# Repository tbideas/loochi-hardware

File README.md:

Hardware source files for TBIdeas lamp
======================================

This github project contains the source file for the different revisions and prototypes of our smart lamp called Illumi and then Loochi.

## License

    Copyright 2012 - TBIdeas.com
    Distributed under the CC-BY-SA license.
    http://creativecommons.org/licenses/by-sa/3.0/

## Loochi v0.4

Third prototype.

This one is very similar to 0.3 but instead of a Bluegiga BLE112 module, we use an Aircable module with its generic firmware (so it does not need any programming). This module is not yet publicly available but will be very soon. Until then, you can contact us if you would like to get some.

In this design, we have also removed the npn/pnp transistors that were used to drive the mosfet. We wanted to compare the performance with and without them.

The communication protocol is labeled as I2C between the BLE module and the attiny but you can also do SPI. We have not really decided which one we will stick to.

### Known problems and limitations

This board was designed before we had time to assemble the 0.3 so the same problem applies on the LED pads, and connections.

## Loochi v0.3

Second complete prototype designed and built by us.

There is only one board with the LED soldered directly on the board. The PCB is intended to be an aluminium core PCB. For prototypes we have used traditional FR4 boards (from the awesome oshpark.com). In any case you absolutely need a pretty big heatsink on the other side of the board.

This board design is a major rework over the previous version. The main goal was to reduce manufacturing cost so that more people could enjoy Loochi. Another major design decision was to drop Wifi. We could write a lot about that but the biggest arguments were: (1) Wifi seriously increases the costs of the solution and (2) the efforts required by the user to set-up a Wifi lamp are important.

Main characteristics:
 * One ATTiny 861A is used to control the current going through the LED and adjust the brightness
 * One BLE112 module from Bluegiga is used for Bluetooth Low Energy communication with the app, it acts as an SPI Master to the Attiny
 * There is no more dedicated chip for the LED PWM (to reduce costs)
 * Ledengin 10W RGGB Led soldered directly on the PCB
 * Funny fact: the board radius is 3.1415925 cm

You will find more information on how this board works in the source code of the AVR. Several versions are provided (with graduating levels of complexity).

We also plan to do a video to explain how it works. If you are interested, let us know and it will probably be done quicker!

### Known problems on the board layout

There are a few known problems on this PCB:
 * The LED footprint is wrong: the first green LED is backwards (stupid mistake when linking pads and signals)
 * The schematic uses the RESET pin of the uController but we decided later on to change that, the mapping used in the software is BSENSE connected to PB5 and BPWM connected to PB4 (which means the Blue PWM output is inverted but allows us to keep the RESET pin free)
 * The BLE112 module is very sensitive to the quality of the power supply, add an RC filter on its VCC
 * Remove Q4 and short its source and drain (otherwise you will get a shortcut) - Warning: this removes the reverse voltage protection

If you want to make your own, we suggest that you fix those before getting the board manufactured or wait for a new design from us that would not have those problems. Another option is always to cut some traces and put some small wires. This is what we have done.

## Illumi v0.2

__Note: We used to call this version Illumi - dont be surprised in the documentation and source code__

This is the first complete prototype completely designed and built by us.

It is a dual-board design: a board with the micro-controller and the Wifi card, and another board with the LED drivers.

Features of the motherboard:

 * Arduino-Leonardo clone running at 8Mhz - Programmable via a ICSP connector or through the USB cable (once the bootloader has been burnt). You can use the Arduino IDE to program it.
 * Wifi module RN-171 from Roving Networks with a wire antenna
 * Bluetooth 4 Low Energy BLE112 module from Bluegiga
 * Only 75mm by 50mm
 * Switching 3.3 V power supply
 
Features of the LED driver

 * Input voltage from ~5V to 20V (depends on the type of LED you want to power) - Compatible with all sorts of high power LEDs
 * Three LT3518 swiching regulator for a 700mA constant current source to drive one RGB led
 * PWM inputs to control the brightness of each component: Red, Green, Blue
 * Shutdown pin to turn off the regulators and save power
 * Three temperature sensors to measure the board temperature

### Files

 * illumi-motherboard.sch: Eagle Schematic for the motherboard
 * illumi-motherboard.sch: Eagle Board for the motherboard
 * illumi-leddriver.sch: Eagle Schematic for the LED Driver
 * illumi-leddriver.sch: Eagle Board for the LED Driver
 * illumi-leddriver.asc: LTSpice simulation for one LT3518 channel 
 * illumi-v0.2-bom.csv: Bill of material - Detailed list of parts with Mouser reference number, price, etc

### Other resources

 * Source code for the motherboard is available in the Github project named "illumi"
 * Configuration files for the Arduino environment to program this board is in the project named "illumi-arduino"
 * Blog articles:
 ** [3D renderings][blog-board3d]
 ** [Pictures of the assembled board][blog-v0.2]

### Known problems and limitations

 * On the motherboard, you must not solder R16 and bridge the pads instead. The idea was to build a low-pass filter with R16 and C13 but the voltage drop on AVCC is too high and the chip is not programmable with R16 in place. Check out [this discussion on electronics stackexchange][stackexchange-avcc] for more info.
 * The LED driver includes a LM317 to provide 3.3V to the three LT3518. Although they dont use much current, bringing a 20V input to 3.3V incurs some serious heat dissipation on the LM317. It works so far but the next designs will use the motherboard voltage regulator for 3.3V

## Illumi v0.1

This is a very cheap to build linear current source for high power RGB LEDs. Find out more and read more on the [blog article][blog-v0.1]. 

## Illumi v0.0

This is the simplest way to drive an RGB light. Those files were produced to prepare a [blog post introducing development for Illumi][blog-v0.0].

## Let's stay in touch!

We hope you will find this information useful! We are open-sourcing all of this in the hope that it will be useful to someone else - if it is, or if you have any question, please contact us: contact THE_AROBASE tbideas.com.

[blog-v0.0]: http://www.tbideas.com/blog/illumi-101-iphone-controlled-rgb-light/
[blog-v0.1]: http://www.tbideas.com/blog/build-an-arduino-shield-to-drive-high-power-rgb-led/
[stackexchange-avcc]: http://electronics.stackexchange.com/questions/36167/understanding-the-avcc-pin-wiring-on-arduinoleonardo-low-pass-filter
[blog-v0.2]: http://www.tbideas.com/blog/some-pictures-of-our-latest-prototype/
[blog-board3d]: http://www.tbideas.com/blog/design-of-the-led-driver/
[contact]: contact@tbideas.com

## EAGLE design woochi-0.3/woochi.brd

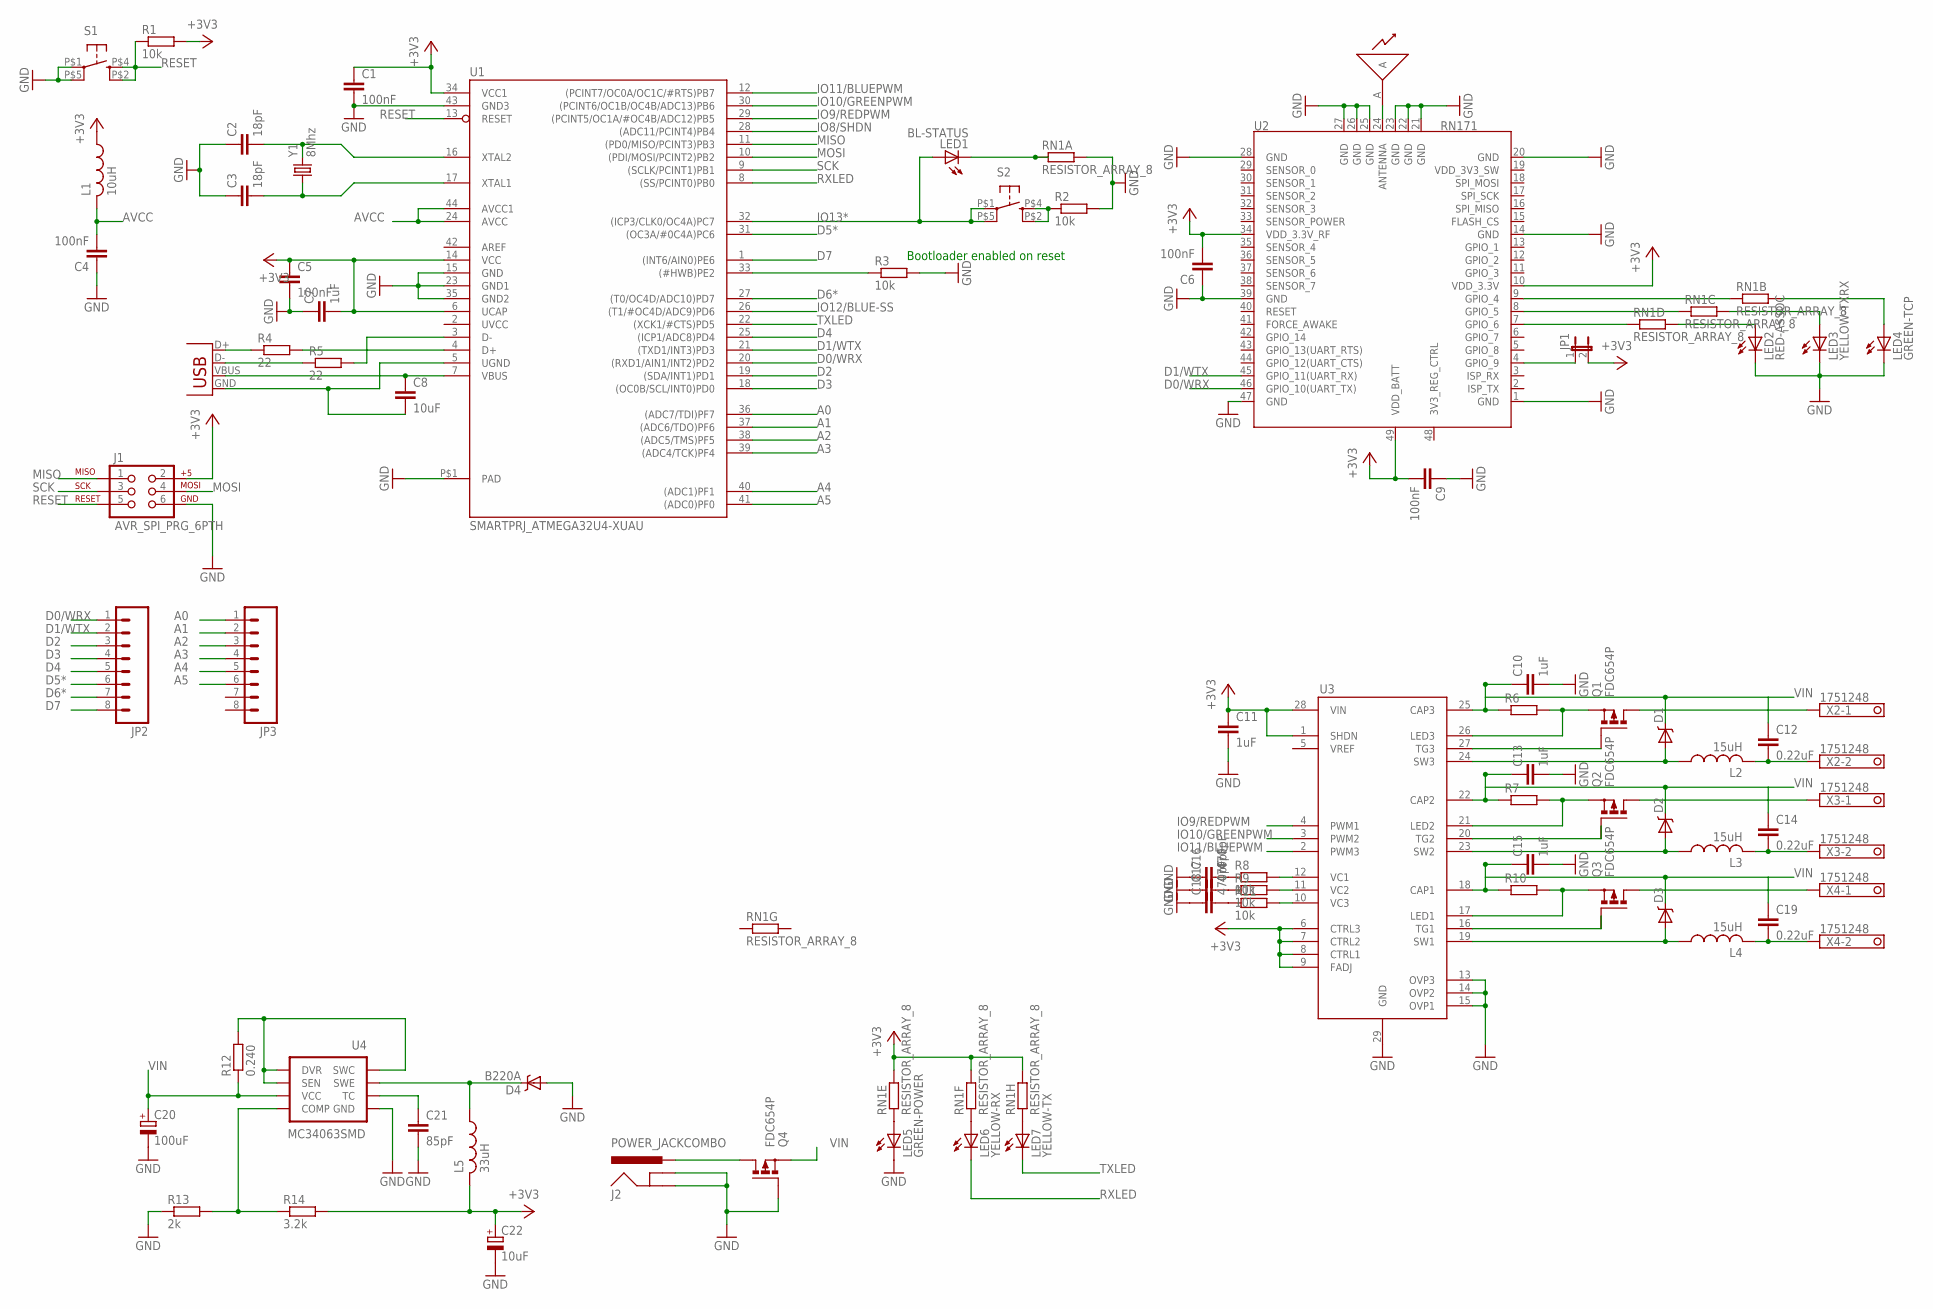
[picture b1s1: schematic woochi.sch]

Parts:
A1: ANTENNAWIRE; ANTENNA-WIRE
C1, C4, C5, C6, C9: 100nF; C0603
C2, C3: 18pF; C0603
C7, C10, C11, C13, C15: 1uF; C0603
C8: 10uF; C0603
C12, C14, C19: 0.22uF; C0603
C16, C17, C18: 470pF; C0603
C20: 100uF; PANASONIC_D
C21: 85pF; C0603
C22: 10uF; PANASONIC_C
D1, D2, D3: DIODE-SCHOTTKYBIGPAD; SMA-DIODE-BIG
D4: B220A; SMA-DIODE-BIG
J1: AVR_SPI_PRG_6PTH; 2X3
J2: POWER_JACKCOMBO; POWER_JACK_COMBO
JP1: JUMPER-2PTH; 1X02
JP2, JP3: M081X08; 1X08
L1: 10uH; L0603
L2, L3, L4: 15uH; BOURNS-6045
L5: 33uH; BOURNS-6045
LED1: BL-STATUS; SML0603
LED2: RED-ASSOC; SML0603
LED3: YELLOW-TXRX; SML0603
LED4: GREEN-TCP; SML0603
LED5: GREEN-POWER; SML0603
LED6: YELLOW-RX; SML0603
LED7: YELLOW-TX; SML0603
Q1, Q2, Q3, Q4: FDC654P; SUPERSOT6
R1, R2, R3, R8, R9, R11: 10k; R0603
R4, R5: 22; R0603
R6, R7, R10: R-EU_R0603; R0603
R12: 0.240; R0603
R13: 2k; R0603
R14: 3.2k; R0603
RN1: RESISTOR_ARRAY_8; CAT16-F8/CAT16-J8
S1, S2: TAC_SWITCH; CK-KMS_PEGS
U1: SMARTPRJ_ATMEGA32U4-XUAU; SMARTPRJ_TQFP44-PAD
U2: RN171; MODULE_49P-1.27-26.67X17.78
U3: LT3496; SSOP28_THERMAL
U4: MC34063SMD; SO08
X1: USB-MICROB
X2, X3, X4: 1751248
Y1: 8Mhz; HC49UP

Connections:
+3V3: C1.1, C5.1, C6.2, C7.2, C9.2, C11.1, C22.+, J1.2, JP1.2, L1.1, L5.P$2 (2), R1.2, R14.2, RN1.9 (2), RN1.11 (2), RN1.12 (2), U1.6 (UCAP), U1.14 (VCC), U1.34 (VCC1), U2.10 (VDD_3.3V), U2.34 (VDD_3.3V_RF), U2.49 (VDD_BATT), U3.1 (SHDN), U3.6 (CTRL3), U3.7 (CTRL2), U3.8 (CTRL1), U3.9 (FADJ), U3.28 (VIN)
A0: JP3.1, U1.36 ((ADC7/TDI)PF7)
A1: JP3.2, U1.37 ((ADC6/TDO)PF6)
A2: JP3.3, U1.38 ((ADC5/TMS)PF5)
A3: JP3.4, U1.39 ((ADC4/TCK)PF4)
A4: JP3.5, U1.40 ((ADC1)PF1)
A5: JP3.6, U1.41 ((ADC0)PF0)
AREF: U1.42 (AREF)
AVCC: C4.2, L1.2, U1.24 (AVCC), U1.44 (AVCC1)
D0/WRX: JP2.1, U1.20 ((RXD1/AIN1/INT2)PD2), U2.46 (GPIO_10(UART_TX))
D1/WTX: JP2.2, U1.21 ((TXD1/INT3)PD3), U2.45 (GPIO_11(UART_RX))
D2: JP2.3, U1.19 ((SDA/INT1)PD1)
D3: JP2.4, U1.18 ((OC0B/SCL/INT0)PD0)
D4: JP2.5, U1.25 ((ICP1/ADC8)PD4)
D5*: JP2.6, U1.31 ((OC3A/#0C4A)PC6)
D6*: JP2.7, U1.27 ((T0/OC4D/ADC10)PD7)
D7: JP2.8, U1.1 ((INT6/AIN0)PE6)
GND: C1.2, C2.1, C3.1, C4.1, C5.2, C6.1, C7.1, C9.1, C10.2, C11.2, C13.2, C15.2, C16.1, C17.1, C18.1, C20.-, C21.2, C22.-, D4.A, J1.6, J2.GND (GNDBREAK), J2.GND@1 (GND), LED2.C, LED3.C, LED4.C, LED5.C, Q4.P$3 (G), R2.2, R3.2, R13.1, RN1.16 (2), S1.P$1 (1), S1.P$5 (2), U1.15 (GND), U1.23 (GND1), U1.35 (GND2), U1.43 (GND3), U1.P$1 (PAD), U2.1 (GND), U2.14 (GND), U2.20 (GND), U2.21 (GND), U2.22 (GND), U2.23 (GND), U2.25 (GND), U2.26 (GND), U2.27 (GND), U2.28 (GND), U2.39 (GND), U2.47 (GND), U3.13 (OVP3), U3.14 (OVP2), U3.15 (OVP1), U3.29 (GND), U4.4 (GND)
IO8/SHDN: U1.28 ((ADC11/PCINT4)PB4)
IO9/REDPWM: U1.29 ((PCINT5/OC1A/#OC4B/ADC12)PB5), U3.4 (PWM1)
IO10/GREENPWM: U1.30 ((PCINT6/OC1B/OC4B/ADC13)PB6), U3.3 (PWM2)
IO11/BLUEPWM: U1.12 ((PCINT7/OC0A/OC1C/#RTS)PB7), U3.2 (PWM3)
IO12/BLUE-SS: U1.26 ((T1/#OC4D/ADC9)PD6)
IO13*: LED1.A, S2.P$1 (1), S2.P$5 (2), U1.32 ((ICP3/CLK0/OC4A)PC7)
MISO: J1.1, U1.11 ((PD0/MISO/PCINT3)PB3)
MOSI: J1.4, U1.10 ((PDI/MOSI/PCINT2)PB2)
unnamed: LED5.A, RN1.5 (1)
unnamed: A1.A, U2.24 (ANTENNA)
unnamed: RN1.2 (1), U2.9 (GPIO_4)
unnamed: RN1.3 (1), U2.8 (GPIO_5)
unnamed: RN1.4 (1), U2.7 (GPIO_6)
unnamed: LED2.A, RN1.13 (2)
unnamed: LED3.A, RN1.14 (2)
unnamed: LED4.A, RN1.15 (2)
unnamed: C8.2, U1.5 (UGND), X1.GND
unnamed: R4.1, X1.D+
unnamed: JP1.1, U2.4 (GPIO_9)
unnamed: R5.1, X1.D-
unnamed: C8.1, U1.7 (VBUS), X1.VBUS
unnamed: R4.2, U1.4 (D+)
unnamed: R5.2, U1.3 (D-)
unnamed: LED1.C, RN1.1
unnamed: LED6.A, RN1.6 (1)
unnamed: LED7.A, RN1.8 (1)
unnamed: R3.1, U1.33 ((#HWB)PE2)
unnamed: R12.2, U4.1 (SWC), U4.7 (SEN), U4.8 (DVR)
unnamed: J2.POWER (PWR), Q4.P$1 (D), Q4.P$2 (D), Q4.P$5 (D), Q4.P$6 (D)
unnamed: D4.C, L5.P$1 (1), U4.2 (SWE)
unnamed: R2.1, S2.P$2 (4), S2.P$4 (3)
unnamed: C21.1, U4.3 (TC)
unnamed: R13.2, R14.1, U4.5 (COMP)
unnamed: C12.2, L2.P$2 (2), X2.2
unnamed: Q1.P$4 (S), R6.2, U3.26 (LED3)
unnamed: D1.A, L2.P$1 (1), U3.24 (SW3)
unnamed: Q2.P$4 (S), R7.2, U3.21 (LED2)
unnamed: Q1.P$1 (D), Q1.P$2 (D), Q1.P$5 (D), Q1.P$6 (D), X2.1
unnamed: Q1.P$3 (G), U3.27 (TG3)
unnamed: C14.2, L3.P$2 (2), X3.2
unnamed: R11.2, U3.10 (VC3)
unnamed: R9.2, U3.11 (VC2)
unnamed: R8.2, U3.12 (VC1)
unnamed: C16.2, R8.1
unnamed: C17.2, R9.1
unnamed: C18.2, R11.1
unnamed: D2.A, L3.P$1 (1), U3.23 (SW2)
unnamed: Q2.P$3 (G), U3.20 (TG2)
unnamed: Q2.P$1 (D), Q2.P$2 (D), Q2.P$5 (D), Q2.P$6 (D), X3.1
unnamed: Q3.P$4 (S), R10.2, U3.17 (LED1)
unnamed: C19.2, L4.P$2 (2), X4.2
unnamed: D3.A, L4.P$1 (1), U3.19 (SW1)
unnamed: Q3.P$3 (G), U3.16 (TG1)
unnamed: Q3.P$1 (D), Q3.P$2 (D), Q3.P$5 (D), Q3.P$6 (D), X4.1
RESET: R1.1, S1.P$2 (4), S1.P$4 (3), U1.13 (RESET)
RXLED: LED6.C, U1.8 ((SS/PCINT0)PB0)
SCK: J1.3, U1.9 ((SCLK/PCINT1)PB1)
TXLED: LED7.C, U1.22 ((XCK1/#CTS)PD5)
UVCC: U1.2 (UVCC)
VIN: C10.1, C12.1, C13.1, C14.1, C15.1, C19.1, C20.+, D1.C, D2.C, D3.C, Q4.P$4 (S), R6.1, R7.1, R10.1, R12.1, U3.18 (CAP1), U3.22 (CAP2), U3.25 (CAP3), U4.6 (VCC)
XTAL1: C3.2, U1.17 (XTAL1), Y1.1
XTAL2: C2.2, U1.16 (XTAL2), Y1.2

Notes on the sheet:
Bootloader enabled on reset

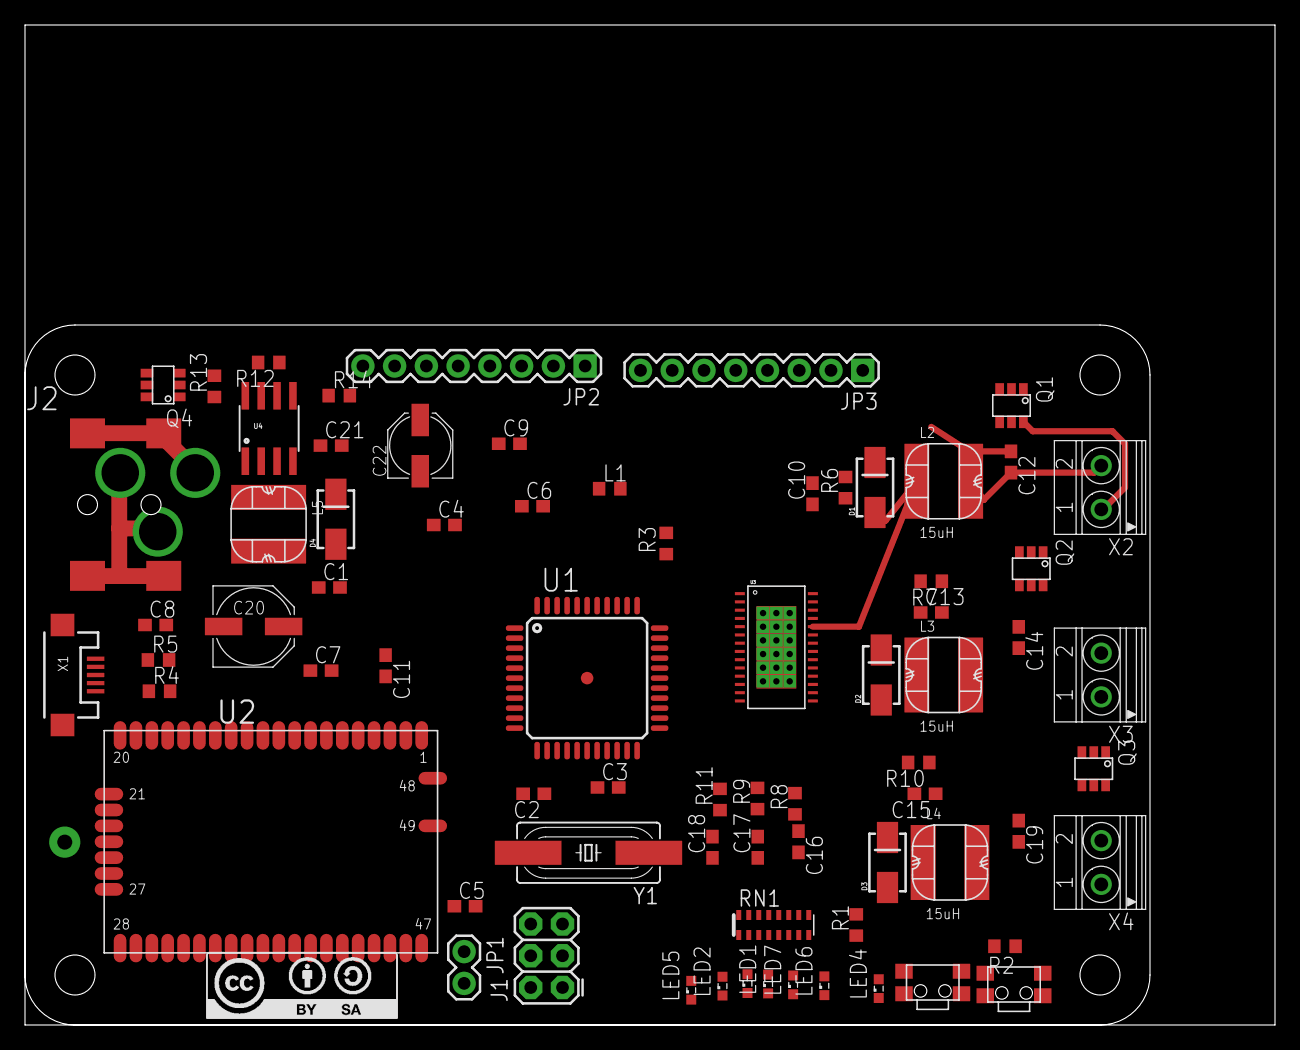
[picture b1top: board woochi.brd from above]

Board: 2 copper layers, 100.0 x 80.0 mm, 76 parts (0 on the bottom side), 76 nets.

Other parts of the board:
U$1: DP9056_V1
U$2: LOGO_CC-BY-SA

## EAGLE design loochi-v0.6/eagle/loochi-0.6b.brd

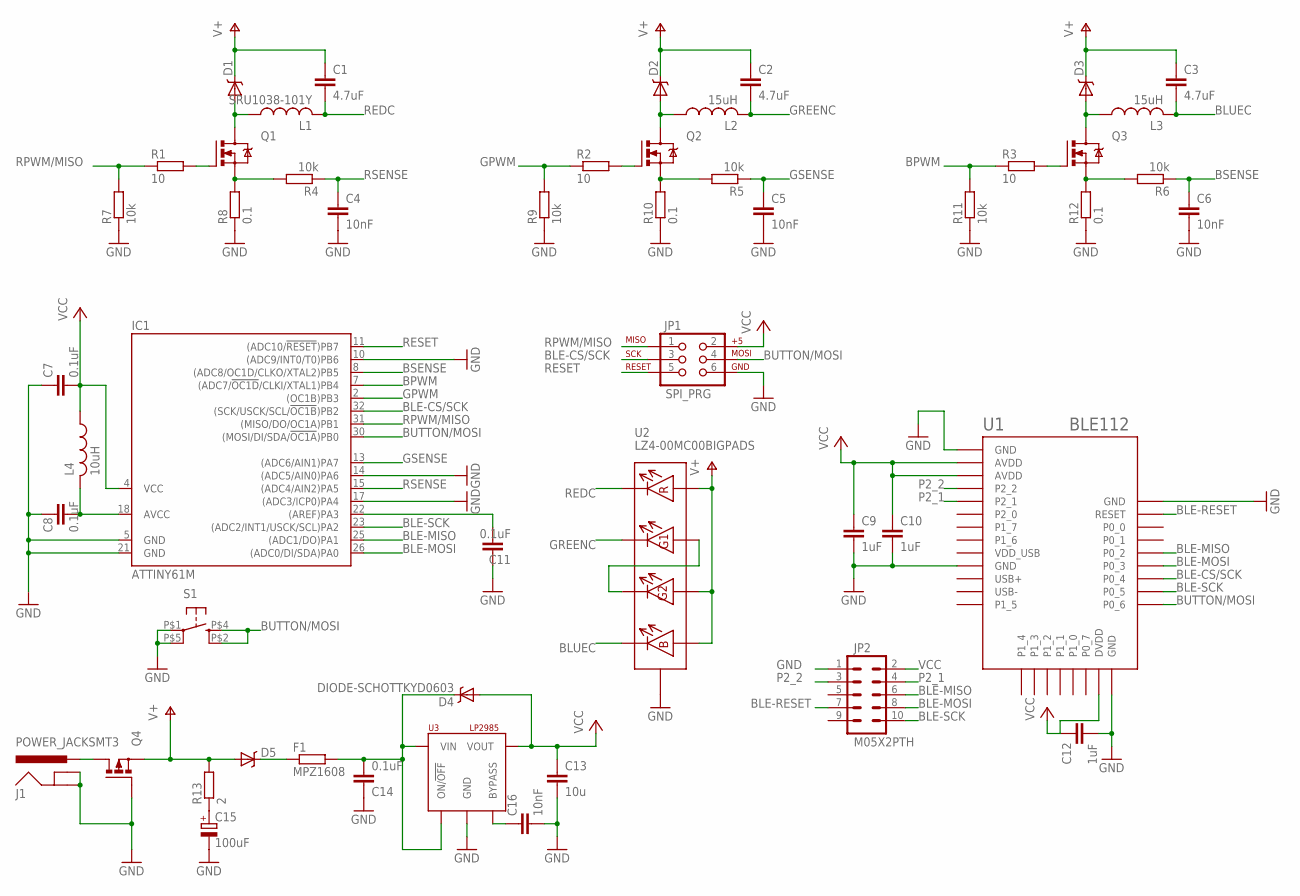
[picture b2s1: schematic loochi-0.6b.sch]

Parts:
C1, C2, C3: 4.7uF; C0603
C4, C5, C6, C16: 10nF; C0603
C7, C8, C11: 0.1uF; C0603
C9, C10, C12: 1uF; C0603
C13: 10u; C0603
C14: 0.1uF; C0603K
C15: 100uF; PANASONIC_D
D1, D2, D3, D5: PMEG4010CEH; SOD123F
D4: DIODE-SCHOTTKYD0603; D0603
F1: MPZ1608; R0603
IC1: ATTINY61M; MLF32
J1: POWER_JACKSMT3; POWER-KYCONSMT3
JP1: SPI_PRG; 2X3-NS
JP2: M05X2PTH; AVR_ICSP
L1: SRU1038-101Y; BOURNS-SRU1038
L2, L3: 15uH; BOURNS-SRU1038
L4: 10uH; L0603
Q1, Q2, Q3: PMN25ENSOT457; SOT457
Q4: FDC654P; SUPERSOT6
R1, R2, R3: 10; R0603
R4, R5, R6, R7, R9, R11: 10k; R0603
R8, R10, R12: 0.1; R0603
R13: 2; R0603
S1: TAC_SWITCH; CK-KMS_PEGS
U1: BLE112; SF-BLUEGIGA_BLE112-A
U2: LZ4-00MC00BIGPADS; LZ4-00MC00-BIGPADS
U3: LP2985; DBV

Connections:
BLE-CS/SCK: IC1.32 ((SCK/USCK/SCL/!OC1B!)PB2), JP1.3, U1.P0_4
BLE-MISO: IC1.25 ((ADC1/DO)PA1), JP2.6, U1.P0_2
BLE-MOSI: IC1.26 ((ADC0/DI/SDA)PA0), JP2.8, U1.P0_3
BLE-RESET: JP2.7, U1.RESET
BLE-SCK: IC1.23 ((ADC2/INT1/USCK/SCL)PA2), JP2.10, U1.P0_5
BLUEC: C3.2, L3.P$2 (2), U2.P$8
BPWM: IC1.7 ((ADC7/!OC1D!/CLKI/XTAL1)PB4), R3.1, R11.2
BSENSE: C6.1, IC1.8 ((ADC8/OC1D/CLKO/XTAL2)PB5), R6.1
BUTTON/MOSI: IC1.30 ((MOSI/DI/SDA/!OC1A!)PB0), JP1.4, S1.P$2 (4), S1.P$4 (3), U1.P0_6
GND: C4.2, C5.2, C6.2, C7.1, C8.1, C9.2, C10.2, C11.1, C12.2, C13.2, C14.1, C15.-, C16.2, IC1.5 (GND), IC1.10 ((ADC9/INT0/T0)PB6), IC1.14 ((ADC5/AIN0)PA6), IC1.17 ((ADC3/ICP0)PA4), IC1.21 (GND), J1.P$2 (GND), J1.P$3 (GNDBREAK), JP1.6, JP2.1, Q4.P$3 (G), R7.1, R8.1, R9.1, R10.1, R11.1, R12.1, S1.P$1 (1), S1.P$5 (2), U1.GND1 (GND), U1.GND2 (GND), U1.GND3 (GND), U1.GND4 (GND), U2.P$9 (THERMAL), U2.THERMAL, U2.THERMAL1 (THERMAL), U2.THERMAL2 (THERMAL), U2.THERMAL3 (THERMAL), U2.THERMAL4 (THERMAL), U2.THERMAL5 (THERMAL), U2.THERMAL6 (THERMAL), U2.THERMAL7 (THERMAL), U2.THERMAL8 (THERMAL), U2.THERMAL9 (THERMAL), U3.2 (GND)
GPWM: IC1.2 ((OC1B)PB3), R2.1, R9.2
GREENC: C2.2, L2.P$2 (2), U2.P$6
GSENSE: C5.1, IC1.13 ((ADC6/AIN1)PA7), R5.1
unnamed: U2.P$2, U2.P$5
unnamed: Q3.P$3 (G), R3.2
unnamed: Q2.P$3 (G), R2.2
unnamed: Q1.P$3 (G), R1.2
unnamed: D5.P$C (C), F1.1
unnamed: Q1.P$4 (S), R4.2, R8.2
unnamed: D1.P$A (A), L1.P$1 (1), Q1.P$1 (D), Q1.P$2 (D), Q1.P$5 (D), Q1.P$6 (D)
unnamed: C11.2, IC1.22 ((AREF)PA3)
unnamed: J1.P$1 (PWR), Q4.P$1 (D), Q4.P$2 (D), Q4.P$5 (D), Q4.P$6 (D)
unnamed: C8.2, IC1.18 (AVCC), L4.2
unnamed: C16.1, U3.4 (BYPASS)
unnamed: D2.P$A (A), L2.P$1 (1), Q2.P$1 (D), Q2.P$2 (D), Q2.P$5 (D), Q2.P$6 (D)
unnamed: Q2.P$4 (S), R5.2, R10.2
unnamed: C15.+, R13.1
unnamed: C14.2, D4.CATHODE (C), F1.2, U3.1 (VIN), U3.3 (ON/!OFF!)
unnamed: D3.P$A (A), L3.P$1 (1), Q3.P$1 (D), Q3.P$2 (D), Q3.P$5 (D), Q3.P$6 (D)
unnamed: Q3.P$4 (S), R6.2, R12.2
P2_1: JP2.4, U1.P2_1
P2_2: JP2.3, U1.P2_2
REDC: C1.2, L1.P$2 (2), U2.P$4
RESET: IC1.11 ((ADC10/!RESET!)PB7), JP1.5
RPWM/MISO: IC1.31 ((MISO/DO/OC1A)PB1), JP1.1, R1.1, R7.2
RSENSE: C4.1, IC1.15 ((ADC4/AIN2)PA5), R4.1
V+: C1.1, C2.1, C3.1, D1.P$C (C), D2.P$C (C), D3.P$C (C), D5.P$A (A), Q4.P$4 (S), R13.2, U2.P$1, U2.P$3, U2.P$7
VCC: C7.2, C9.1, C10.1, C12.1, C13.1, D4.ANODE (A), IC1.4 (VCC), JP1.2, JP2.2, L4.1, U1.AVDD1 (AVDD), U1.AVDD2 (AVDD), U1.DVDD, U3.5 (VOUT)
VDD_USB: U1.VDD_USB

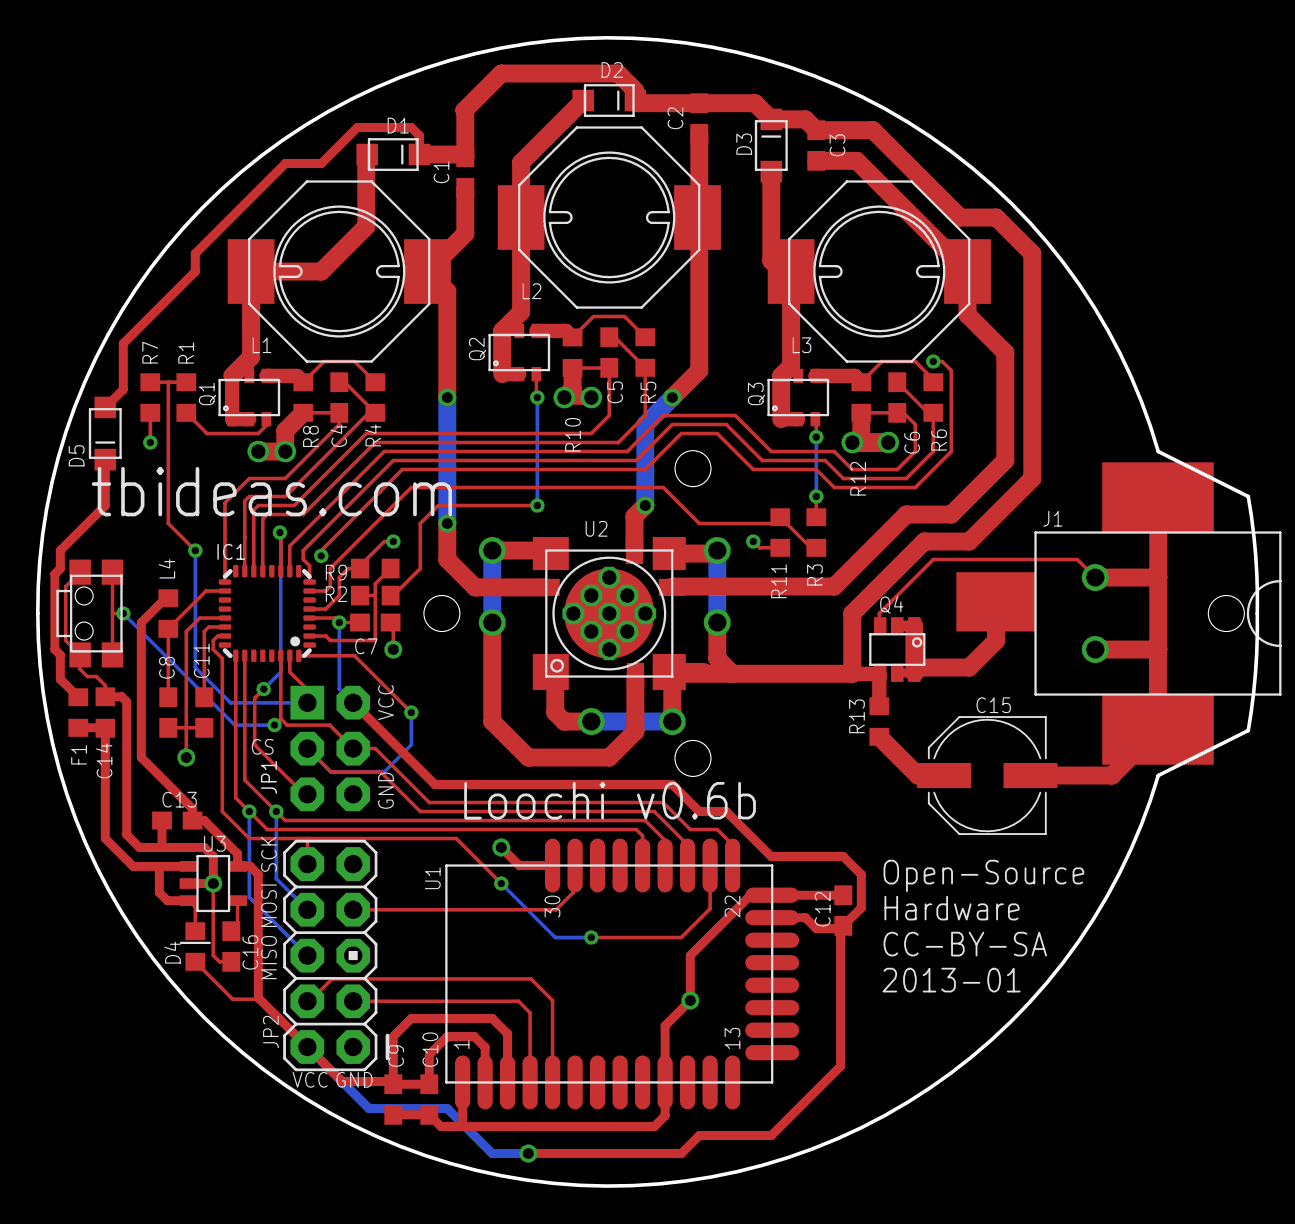
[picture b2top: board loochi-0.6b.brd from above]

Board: 2 copper layers, 67.8 x 63.8 mm, 51 parts (0 on the bottom side), 38 nets.

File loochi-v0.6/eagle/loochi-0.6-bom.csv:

Part,Description,Package,Manufacturer,Mnf. Ref.,Mouser Ref,Qty,Price per unit ($),Price /1000
"C1,C2,C3",4.7uF,C-EUC0603,,,603-CC603KRX5R6BB475,3,0.09,0.023
"C4,C5,C6,C16 (was C17)",10nF,C-EUC0603,,,77-VJ0603Y103KXAAC,4,0.06,0.016
"C7,C8,C11,C14",0.1uF,C-EUC0603,,,77-VJ0603Y104JXJPBC,4,0.06,0.012
"C9,C10,C12",1uF,C-EUC0603,,,77-VJ0603V105MXQPBC,3,0.06,0.009
C13 (was C14),10u,C-EUC0603,,,810-C1608X5R0J106M,1,0.12,0.053
C15 (was C16),100uF,CPOL-EUD,,,598-AVE107M25X16T-F,1,0.13,0.066
"D1,D2,D3,D5",Schottky PMEG4010CEH,SOD123F,,,771-PMEG4010CEH-T/R,3,0.11,0.081
D4,Schottky0603,D0603,Bourns,,652-CD0603-B00340,1,0.12,0.06
F1,MPZ1608,R-EU_R0603,,,810-MPZ1608S221A,1,0.05,0.019
IC1,ATTINY61M,ATTINY61M,MLF32,,556-ATTINY861V10MU,1,3.03,1.72
J1 (was J2),SMD Power connector,POWER-JACK,,KLDXSMT30202BTR,806-KLDXSMT30202BTR,1,1.61,1.05
JP1 (was J1),SPI_PRG,AVR_SPI_PRG_6NS,2X3-NS,,649-68602-406HLF,1,0.12,0
JP2,Molex 5x2,,,,649-68602-110HLF,1,0.3,0.15
"L1,L2,L3",SRU1038-101Y,L-USBOURNS-SRU1038,,,652-SRU1038-101Y,3,0.58,0.32
L4,10uH,L-USL0603,,,810-MLZ1608M100W,1,0.08,0.037
"Q1,Q2,Q3",PMN25ENSOT457,PMN25ENSOT457,,,"771-PMN25EN,115",3,0.14,0.095
Q4,FDC654P,SUPERSOT6,Fairchild Semi.,FDC654P,512-FDC654P,1,0.25,0.12
"R1,R2,R3",10,R-EU_R0603,,,652-CR0603-FX10R0GLF,3,0.04,0.008
"R4,R5,R6,R7,R9,R11",10k,R-EU_R0603,,,652-CR0603-FX1002HLF,6,0.04,0.008
"R8,R10,R12",0.1,R-EU_R0603,,,CRL0603-FW-R100ELF,3,0.08,0.054
R13 (was R15),2,R-EU_R0603,,,301-2.0-RC,1,0.03,0.013
S1,,,,,611-KMS221GLFS,1,0.29,0.25
U1,Ble 112,,,,603-BLE112-A,1,17.5,15.9
U2 (was U1),LZ4-00MC00,,Ledengin,LZ4-00MC00,897-LZ400MC00,1,11.52,9.25
U3 (was U$2),LP2985,LP2985,,,595-LP2985-33DBVR,1,0.46,0.192
Heatsink,,,Lighting Science Group,HS-4075-0345,599-HS-4075-0345,1,19.21,15.99
Total,,,,,,,58.84,46.8

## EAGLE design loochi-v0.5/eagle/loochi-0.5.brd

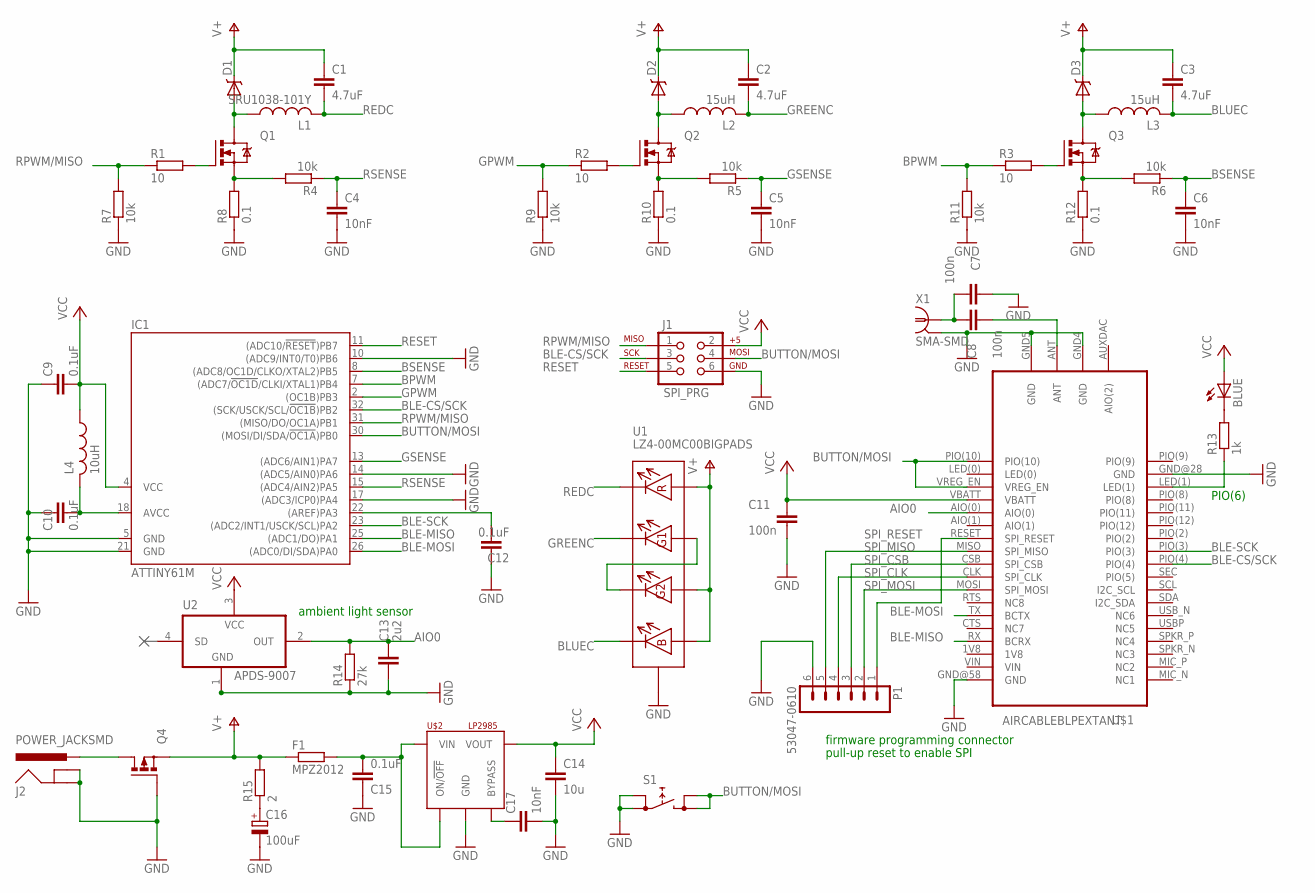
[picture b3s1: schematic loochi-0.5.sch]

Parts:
BLUE: 500003; CHIPLED_0603
C1, C2, C3: 4.7uF; C0603
C4, C5, C6, C17: 10nF; C0603
C7, C8, C11: 100n; C0603; PARTNO *
C9, C10, C12: 0.1uF; C0603
C13: 2u2; C0603; PARTNO *
C14: 10u; C0603
C15: 0.1uF; C0603K
C16: 100uF; PANASONIC_D
D1, D2, D3: PMEG4010CEH; SOD123F
F1: MPZ2012; R0603
IC1: ATTINY61M; MLF32
J1: SPI_PRG; 2X3-NS
J2: POWER_JACKSMD; POWER_JACK_SMD
L1: SRU1038-101Y; BOURNS-SRU1038
L2, L3: 15uH; BOURNS-SRU1038
L4: 10uH; L0603
P1: 53047-0610; PARTNO *
Q1, Q2, Q3: PMN25ENSOT457; SOT457
Q4: FDC654P; SUPERSOT6
R1, R2, R3: 10; R0603
R4, R5, R6, R7, R9, R11: 10k; R0603
R8, R10, R12: 0.1; R0603
R13: 1k; R0603
R14: 27k; R0603
R15: 2; R0603
S1: REKN; TACTSWITCHHORIZONTAL; PARTNO *
U1: LZ4-00MC00BIGPADS; LZ4-00MC00-BIGPADS
U2: APDS-9007; PARTNO *
U$1: AIRCABLEBLPEXTANT; AIRCABLEBLP
U$2: LP2985; DBV
X1: SMA-SMD

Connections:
AIO0: C13.1, R14.2, U2.2 (OUT), U$1.AIO(0)
BLE-CS/SCK: IC1.32 ((SCK/USCK/SCL/!OC1B!)PB2), J1.3, U$1.PIO(4)
BLE-MISO: IC1.25 ((ADC1/DO)PA1), U$1.RX (BCRX)
BLE-MOSI: IC1.26 ((ADC0/DI/SDA)PA0), U$1.TX (BCTX)
BLE-SCK: IC1.23 ((ADC2/INT1/USCK/SCL)PA2), U$1.PIO(3)
BLUEC: C3.2, L3.P$2 (2), U1.P$8
BPWM: IC1.7 ((ADC7/!OC1D!/CLKI/XTAL1)PB4), R3.1, R11.2
BSENSE: C6.1, IC1.8 ((ADC8/OC1D/CLKO/XTAL2)PB5), R6.1
BUTTON/MOSI: IC1.30 ((MOSI/DI/SDA/!OC1A!)PB0), J1.4, S1.3 (1), S1.4 (1), U$1.PIO(10), U$1.VREG_EN
GND: C4.2, C5.2, C6.2, C7.2, C9.1, C10.1, C11.1, C12.1, C13.2, C14.2, C15.1, C16.-, C17.2, IC1.5 (GND), IC1.10 ((ADC9/INT0/T0)PB6), IC1.14 ((ADC5/AIN0)PA6), IC1.17 ((ADC3/ICP0)PA4), IC1.21 (GND), J1.6, J2.GND (GNDBREAK), J2.P$4 (GND), P1.6, Q4.P$3 (G), R7.1, R8.1, R9.1, R10.1, R11.1, R12.1, R14.1, S1.1 (0), S1.2 (0), U1.P$9 (THERMAL), U1.THERMAL, U1.THERMAL1 (THERMAL), U1.THERMAL2 (THERMAL), U1.THERMAL3 (THERMAL), U1.THERMAL4 (THERMAL), U1.THERMAL5 (THERMAL), U1.THERMAL6 (THERMAL), U1.THERMAL7 (THERMAL), U1.THERMAL8 (THERMAL), U1.THERMAL9 (THERMAL), U2.1 (GND), U$1.GND4 (GND), U$1.GND5 (GND), U$1.GND@28 (GND), U$1.GND@58 (GND), U$2.2 (GND), X1.2@1 (GND), X1.2@2 (GND), X1.2@3 (GND), X1.2@4 (GND), X1.2@5 (GND), X1.2@6 (GND)
GPWM: IC1.2 ((OC1B)PB3), R2.1, R9.2
GREENC: C2.2, L2.P$2 (2), U1.P$6
GSENSE: C5.1, IC1.13 ((ADC6/AIN1)PA7), R5.1
unnamed: U1.P$2, U1.P$5
unnamed: C8.1, U$1.ANT
unnamed: Q3.P$3 (G), R3.2
unnamed: Q2.P$3 (G), R2.2
unnamed: Q1.P$3 (G), R1.2
unnamed: Q1.P$4 (S), R4.2, R8.2
unnamed: D1.P$A (A), L1.P$1 (1), Q1.P$1 (D), Q1.P$2 (D), Q1.P$5 (D), Q1.P$6 (D)
unnamed: C12.2, IC1.22 ((AREF)PA3)
unnamed: J2.VIN0 (PWR), J2.VIN1 (PWR), Q4.P$1 (D), Q4.P$2 (D), Q4.P$5 (D), Q4.P$6 (D)
unnamed: C10.2, IC1.18 (AVCC), L4.2
unnamed: BLUE.C, R13.2
unnamed: C17.1, U$2.4 (BYPASS)
unnamed: D2.P$A (A), L2.P$1 (1), Q2.P$1 (D), Q2.P$2 (D), Q2.P$5 (D), Q2.P$6 (D)
unnamed: C7.1, C8.2, X1.1
unnamed: R13.1, U$1.LED(1)
unnamed: Q2.P$4 (S), R5.2, R10.2
unnamed: C16.+, R15.1
unnamed: C15.2, F1.2, U$2.1 (VIN), U$2.3 (ON/!OFF!)
unnamed: D3.P$A (A), L3.P$1 (1), Q3.P$1 (D), Q3.P$2 (D), Q3.P$5 (D), Q3.P$6 (D)
unnamed: Q3.P$4 (S), R6.2, R12.2
REDC: C1.2, L1.P$2 (2), U1.P$4
RESET: IC1.11 ((ADC10/!RESET!)PB7), J1.5
RPWM/MISO: IC1.31 ((MISO/DO/OC1A)PB1), J1.1, R1.1, R7.2
RSENSE: C4.1, IC1.15 ((ADC4/AIN2)PA5), R4.1
SPI_CLK: P1.4, U$1.CLK (SPI_CLK)
SPI_CSB: P1.3, U$1.CSB (SPI_CSB)
SPI_MISO: P1.5, U$1.MISO (SPI_MISO)
SPI_MOSI: P1.2, U$1.MOSI (SPI_MOSI)
SPI_RESET: P1.1, U$1.RESET (SPI_RESET)
V+: C1.1, C2.1, C3.1, D1.P$C (C), D2.P$C (C), D3.P$C (C), F1.1, Q4.P$4 (S), R15.2, U1.P$1, U1.P$3, U1.P$7
VCC: BLUE.A, C9.2, C11.2, C14.1, IC1.4 (VCC), J1.2, L4.1, U2.3 (VCC), U$1.VBATT, U$2.5 (VOUT)

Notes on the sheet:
firmware programming connector
pull-up reset to enable SPI
ambient light sensor
PIO(6)

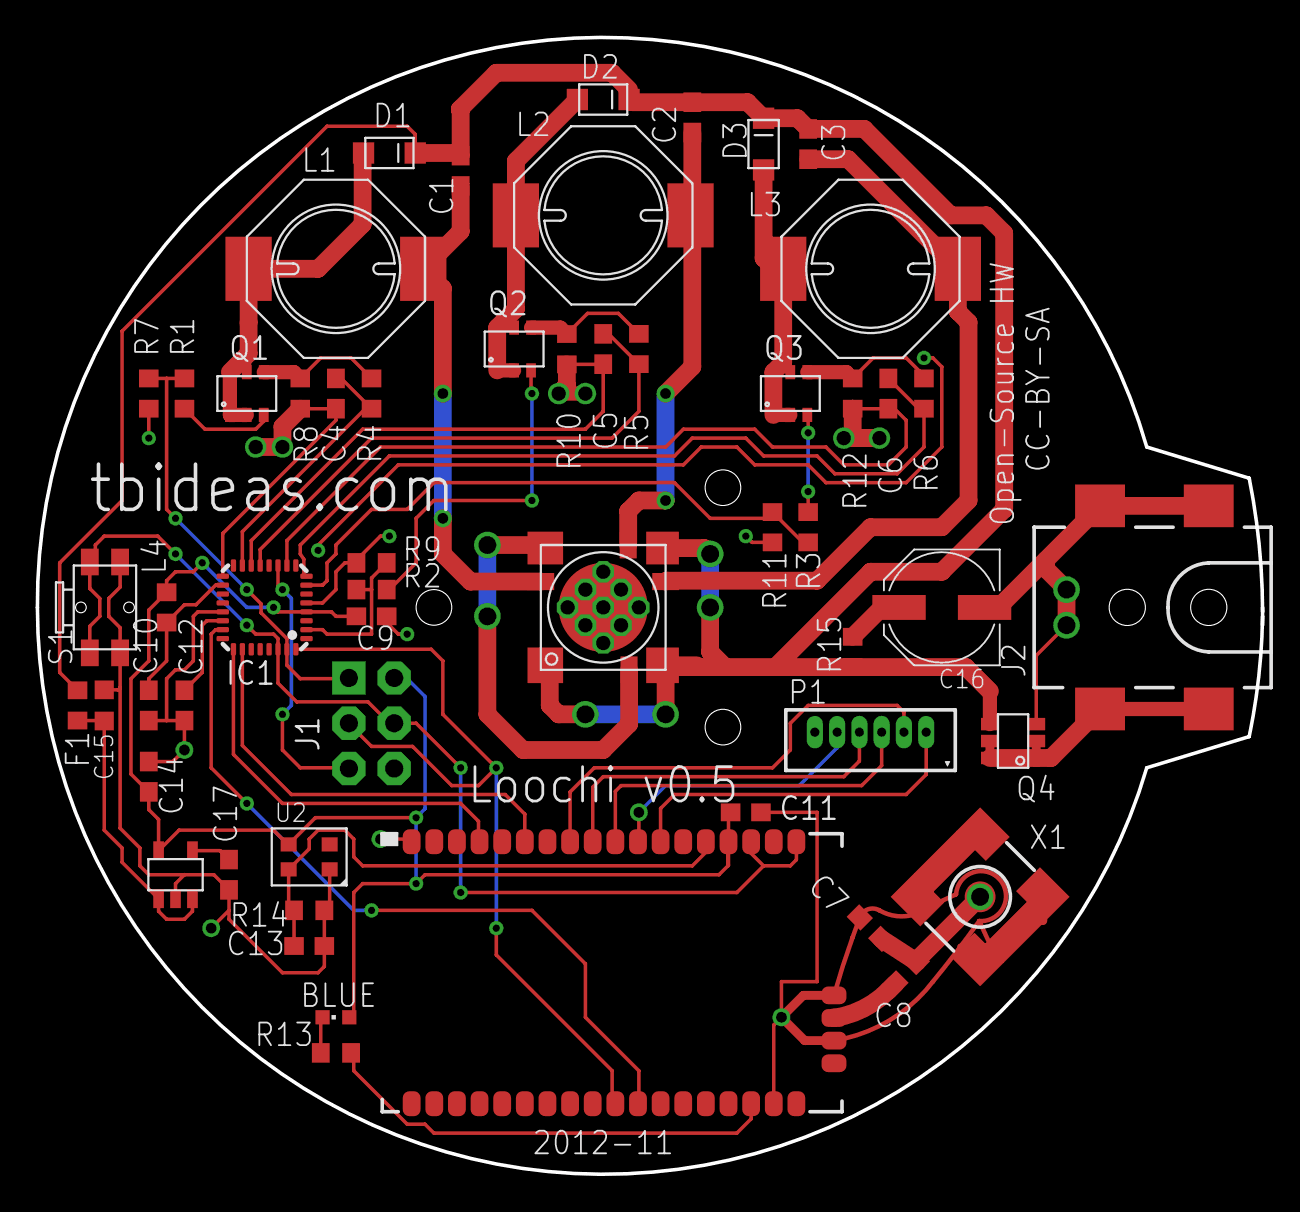
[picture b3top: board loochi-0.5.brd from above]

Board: 2 copper layers, 68.8 x 63.8 mm, 55 parts (0 on the bottom side), 44 nets.

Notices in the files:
parts and their libraries:
SparkFun: Licensing: CC v3.0 Share-Alike You are welcome to use this library for commercial purposes.
